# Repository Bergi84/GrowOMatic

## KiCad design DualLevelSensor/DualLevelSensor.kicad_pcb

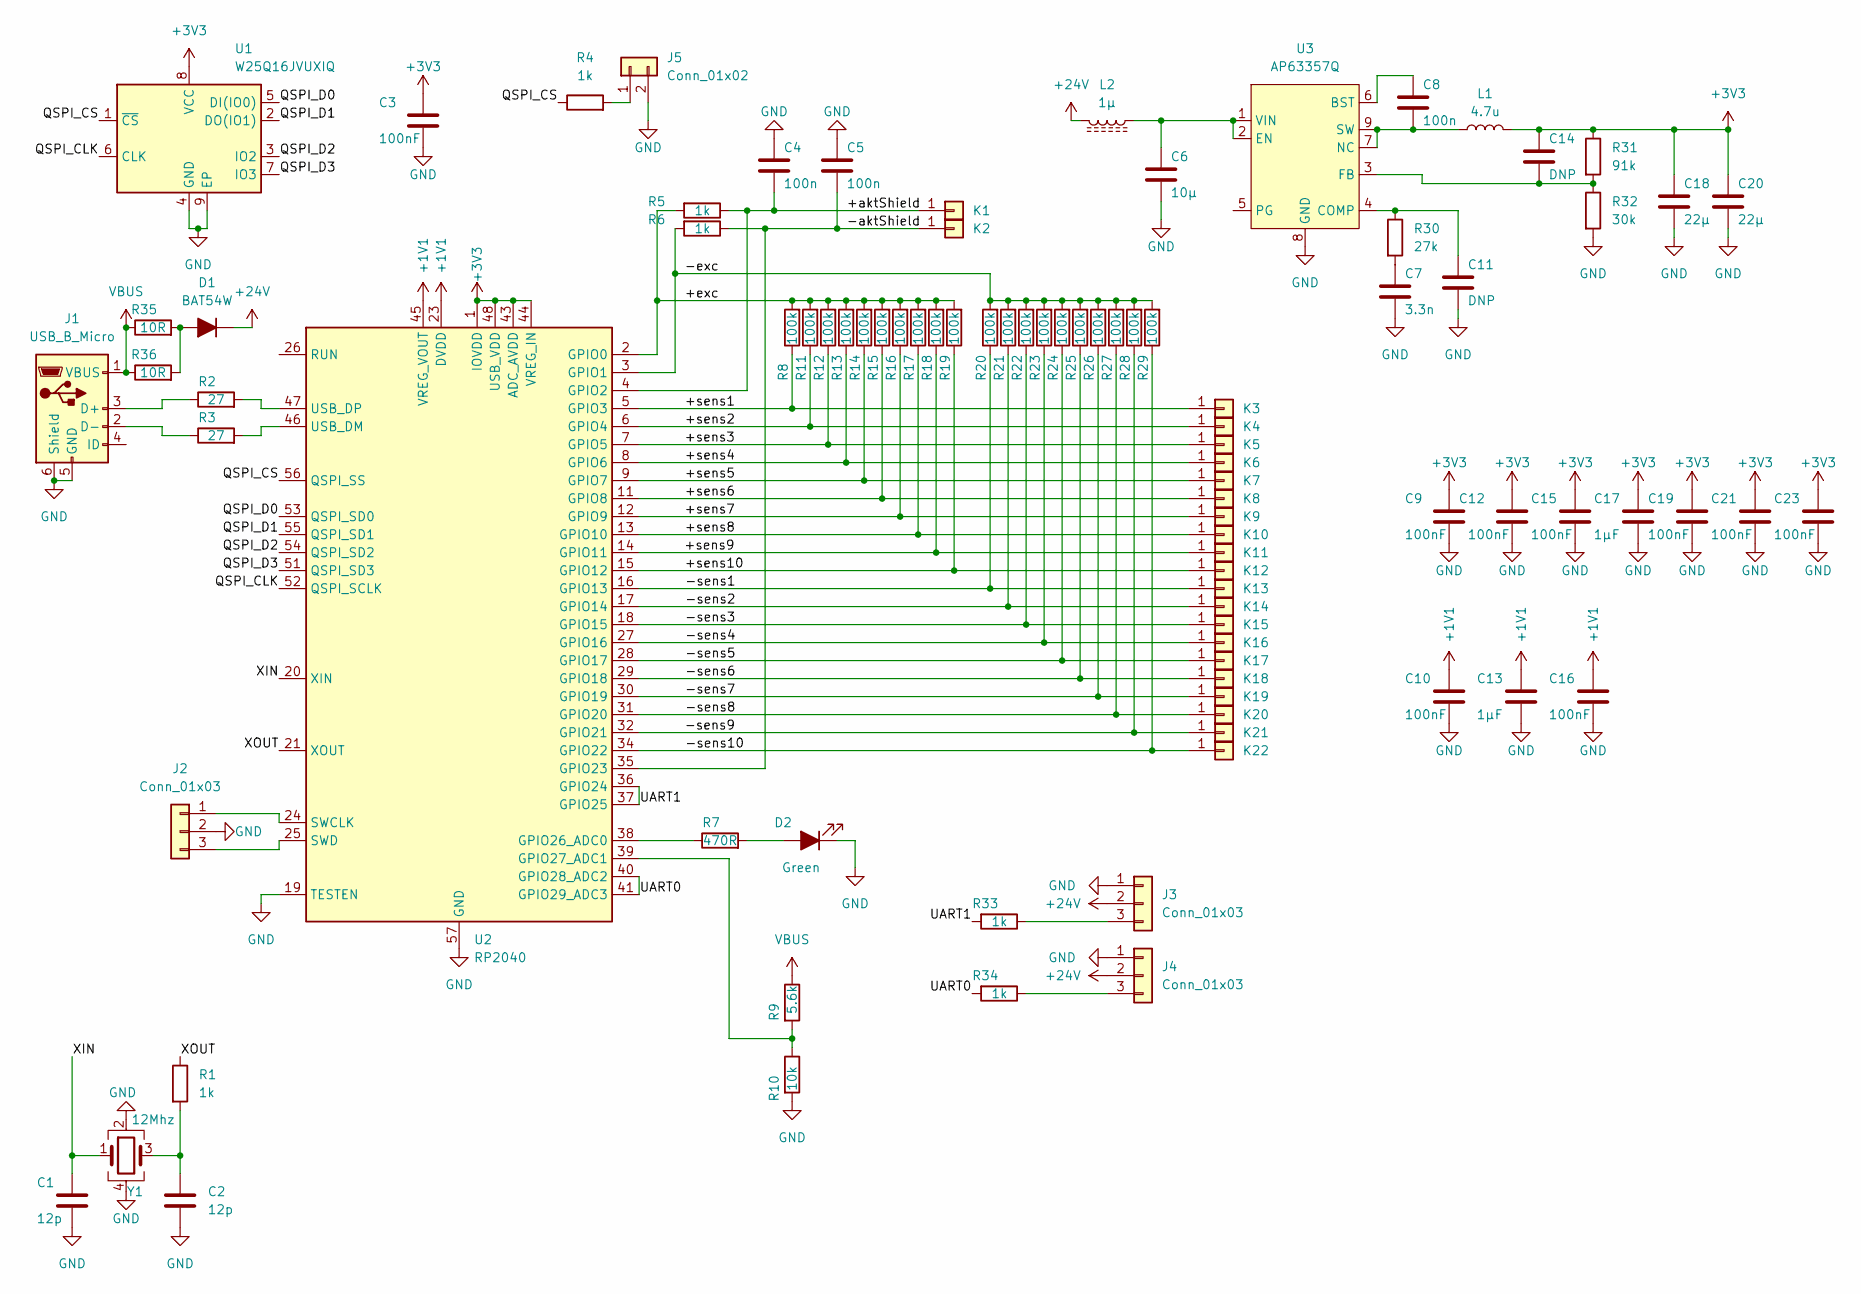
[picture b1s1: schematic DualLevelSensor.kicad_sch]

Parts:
C1, C2: 12p; C_0603_1608Metric
C3, C9, C10, C12, C15, C16, C19, C21, C23: 100nF; C_0603_1608Metric
C4, C5, C8: 100n; C_0603_1608Metric
C6: 10µ; C_1210_3225Metric
C7: 3.3n; C_0603_1608Metric
C11, C14: DNP; C_0603_1608Metric
C13, C17: 1µF; C_0603_1608Metric
C18, C20: 22µ; C_1206_3216Metric
D1: BAT54W; D_SOD-323
D2: Green; LED_0603_1608Metric
J1: USB_B_Micro; USB_Micro-B_GCT_USB3076-30-A
J2: Conn_01x03; PinHeader_1x03_P2.54mm_Vertical
J3, J4: Conn_01x03; Molex_KK-254_AE-6410-03A_1x03_P2.54mm_Vertical
J5: Conn_01x02; PinSocket_1x02_P2.54mm_Vertical
K1, K2, K3, K4, K5, K6, K7, K8, K9, K10, K11, K12, K13, K14, K15, K16, K17, K18, K19, K20, K21, K22: capPad; dummyPad
L1: 4.7u; L_1008_2520Metric
L2: 1µ; L_0805_2012Metric
R1, R4, R5, R6, R33, R34: 1k; R_0603_1608Metric
R2, R3: 27; R_0603_1608Metric
R7: 470R; R_0603_1608Metric
R8, R11, R12, R13, R14, R15, R16, R17, R18, R19, R20, R21, R22, R23, R24, R25, R26, R27, R28, R29: 100k; R_0603_1608Metric
R9: 5.6k; R_0603_1608Metric
R10: 10k; R_0603_1608Metric
R30: 27k; R_0603_1608Metric
R31: 91k; R_0603_1608Metric
R32: 30k; R_0603_1608Metric
R35, R36: 10R; R_0603_1608Metric
U1: W25Q16JVUXIQ; DFN-8-1EP_3x2mm_P0.5mm_EP0.3x1.6mm
U2: RP2040; QFN-56-1EP_7x7mm_P0.4mm_EP3.2x3.2mm
U3: AP63357Q; V-DFN3020-13
Y1: 12Mhz; Crystal_SMD_2520-4Pin_2.5x2.0mm

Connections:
+1V1: C10.1, C13.1, C16.1, U2.23 (DVDD), U2.45 (VREG_VOUT), U2.50 (DVDD)
+3V3: C3.1, C9.1, C12.1, C14.2, C15.1, C17.1, C18.2, C19.1, C20.2, C21.1, C23.1, L1.2, R31.1, U1.8 (VCC), U2.1 (IOVDD), U2.10 (IOVDD), U2.22 (IOVDD), U2.33 (IOVDD), U2.42 (IOVDD), U2.43 (ADC_AVDD), U2.44 (VREG_IN), U2.48 (USB_VDD), U2.49 (IOVDD)
+24V: D1.1 (K), J3.2, J4.2, L2.2
/+aktShield: C4.1, K1.1, R5.1, U2.4 (GPIO2)
/+exc: R5.2, R8.2, R11.2, R12.2, R13.2, R14.2, R15.2, R16.2, R17.2, R18.2, R19.2, U2.2 (GPIO0)
/+sens1: K3.1, R8.1, U2.5 (GPIO3)
/+sens2: K4.1, R11.1, U2.6 (GPIO4)
/+sens3: K5.1, R12.1, U2.7 (GPIO5)
/+sens4: K6.1, R13.1, U2.8 (GPIO6)
/+sens5: K7.1, R14.1, U2.9 (GPIO7)
/+sens6: K8.1, R15.1, U2.11 (GPIO8)
/+sens7: K9.1, R16.1, U2.12 (GPIO9)
/+sens8: K10.1, R17.1, U2.13 (GPIO10)
/+sens9: K11.1, R18.1, U2.14 (GPIO11)
/+sens10: K12.1, R19.1, U2.15 (GPIO12)
/-aktShield: C5.1, K2.1, R6.1, U2.35 (GPIO23)
/-exc: R6.2, R20.2, R21.2, R22.2, R23.2, R24.2, R25.2, R26.2, R27.2, R28.2, R29.2, U2.3 (GPIO1)
/-sens1: K13.1, R20.1, U2.16 (GPIO13)
/-sens2: K14.1, R21.1, U2.17 (GPIO14)
/-sens3: K15.1, R22.1, U2.18 (GPIO15)
/-sens4: K16.1, R23.1, U2.27 (GPIO16)
/-sens5: K17.1, R24.1, U2.28 (GPIO17)
/-sens6: K18.1, R25.1, U2.29 (GPIO18)
/-sens7: K19.1, R26.1, U2.30 (GPIO19)
/-sens8: K20.1, R27.1, U2.31 (GPIO20)
/-sens9: K21.1, R28.1, U2.32 (GPIO21)
/-sens10: K22.1, R29.1, U2.34 (GPIO22)
/QSPI_CLK: U1.6 (CLK), U2.52 (QSPI_SCLK)
/QSPI_CS: R4.1, U1.1 (~CS), U2.56 (QSPI_SS)
/QSPI_D0: U1.5 (DI(IO0)), U2.53 (QSPI_SD0)
/QSPI_D1: U1.2 (DO(IO1)), U2.55 (QSPI_SD1)
/QSPI_D2: U1.3 (IO2), U2.54 (QSPI_SD2)
/QSPI_D3: U1.7 (IO3), U2.51 (QSPI_SD3)
/UART0: R34.2, U2.40 (GPIO28_ADC2), U2.41 (GPIO29_ADC3)
/UART1: R33.2, U2.36 (GPIO24), U2.37 (GPIO25)
/XIN: C1.1, U2.20 (XIN), Y1.1
/XOUT: R1.1, U2.21 (XOUT)
GND: C1.2, C2.2, C3.2, C4.2, C5.2, C6.1, C7.1, C9.2, C10.2, C11.1, C12.2, C13.2, C15.2, C16.2, C17.2, C18.1, C19.2, C20.1, C21.2, C23.2, D2.1 (K), J1.5 (GND), J1.6 (Shield), J2.2, J3.1, J4.1, J5.2, R10.2, R32.2, U1.4 (GND), U1.9 (EP), U2.19 (TESTEN), U2.57 (GND), U3.8 (GND), Y1.2, Y1.4
unnamed: C2.1, R1.2, Y1.3
unnamed: C6.2, L2.1, U3.1 (VIN), U3.2 (EN)
unnamed: C7.2, R30.2
unnamed: C8.1, L1.1, U3.7 (NC), U3.9 (SW)
unnamed: C8.2, U3.6 (BST)
unnamed: C11.2, R30.1, U3.4 (COMP)
unnamed: C14.1, R31.2, R32.1, U3.3 (FB)
unnamed: D1.2 (A), R35.2, R36.2
unnamed: D2.2 (A), R7.2
unnamed: J1.2 (D-), R3.1
unnamed: J1.3 (D+), R2.1
unnamed: J2.1, U2.24 (SWCLK)
unnamed: J2.3, U2.25 (SWD)
unnamed: J3.3, R33.1
unnamed: J4.3, R34.1
unnamed: J5.1, R4.2
unnamed: R2.2, U2.47 (USB_DP)
unnamed: R3.2, U2.46 (USB_DM)
unnamed: R7.1, U2.38 (GPIO26_ADC0)
unnamed: R9.2, R10.1, U2.39 (GPIO27_ADC1)
VBUS: J1.1 (VBUS), R9.1, R35.1, R36.1

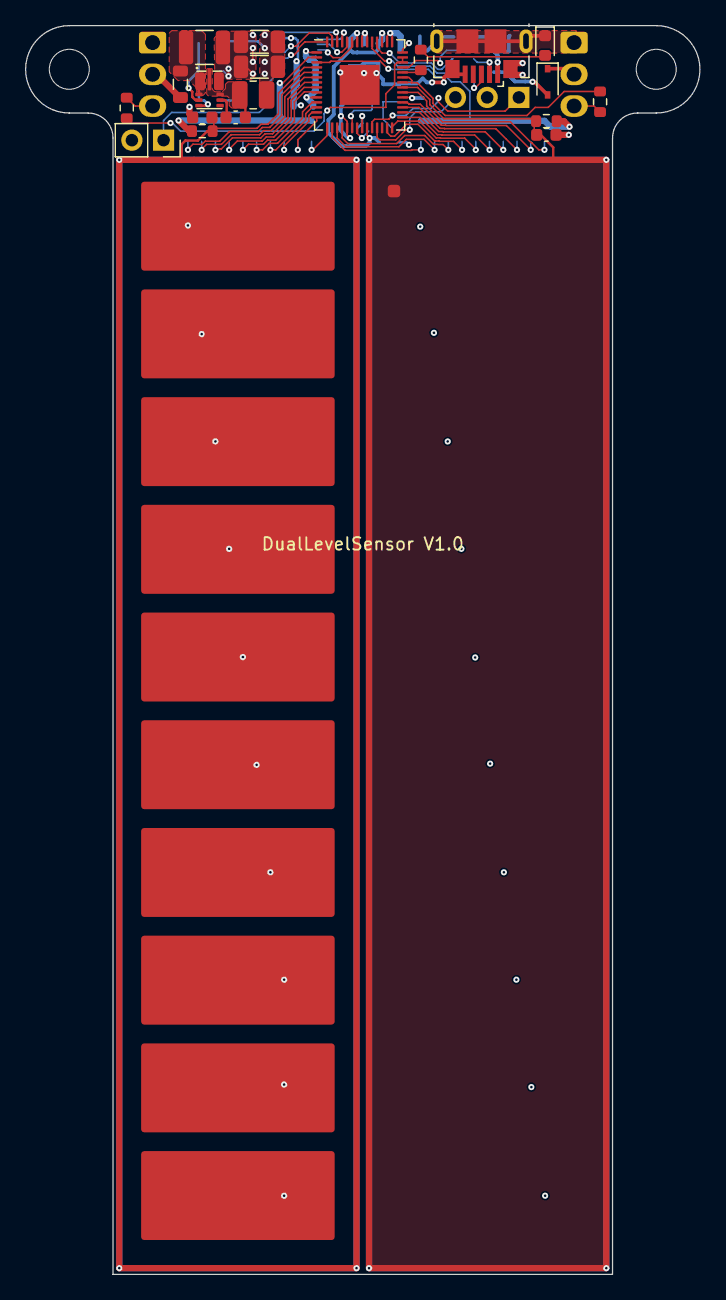
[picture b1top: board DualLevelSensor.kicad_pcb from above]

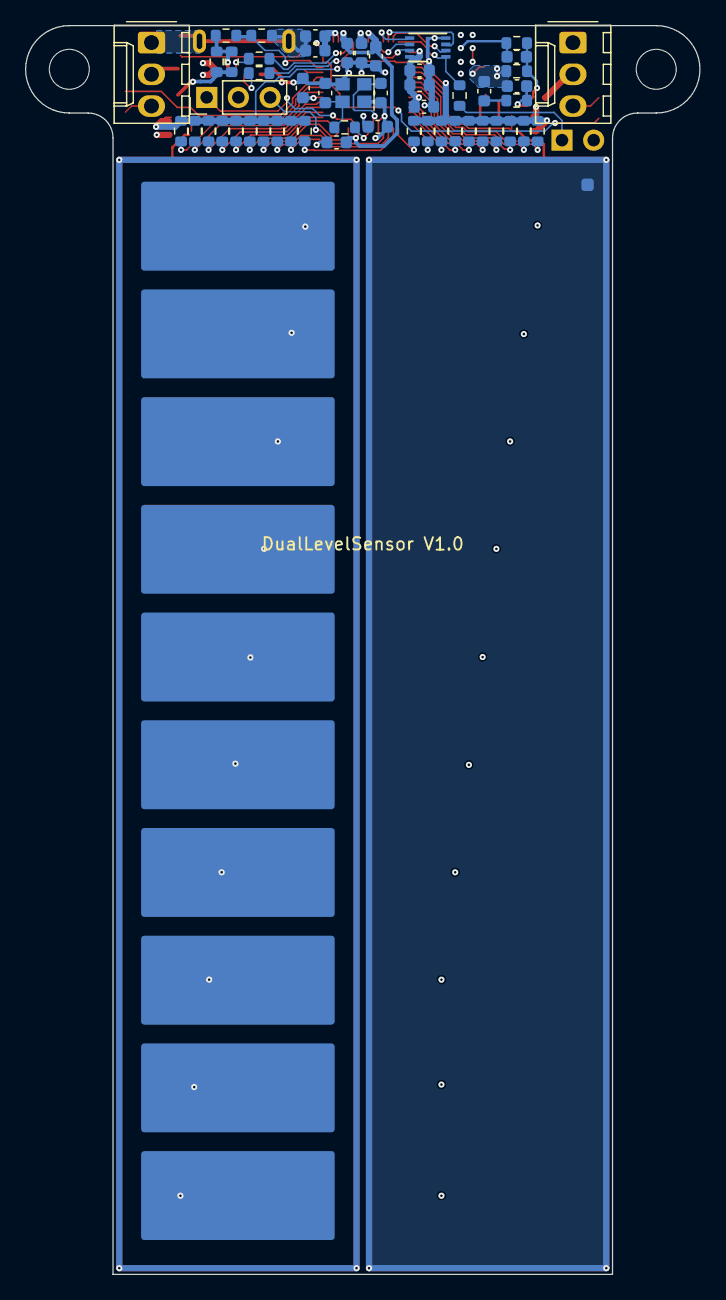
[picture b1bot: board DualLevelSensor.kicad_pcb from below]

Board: 4 copper layers, 54.0 x 100.0 mm, 95 parts (63 on the bottom side), 59 nets.

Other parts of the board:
H1, H2: MountingHole; MountingHole_3.2mm_M3_DIN965

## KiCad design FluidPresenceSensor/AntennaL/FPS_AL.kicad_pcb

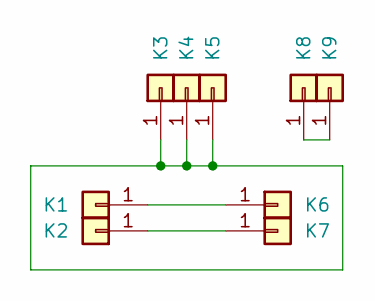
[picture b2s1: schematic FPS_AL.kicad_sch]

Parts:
K1, K2, K3, K4, K5, K6, K7, K8, K9: capPad; dummyPad

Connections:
unnamed: K1.1, K6.1
unnamed: K2.1, K7.1
unnamed: K3.1, K4.1, K5.1
unnamed: K8.1, K9.1

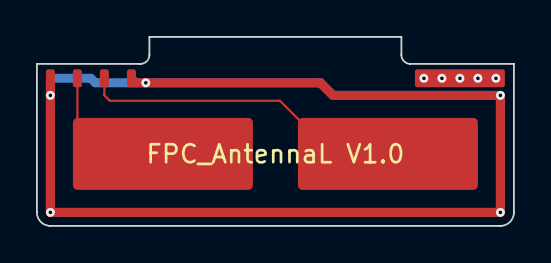
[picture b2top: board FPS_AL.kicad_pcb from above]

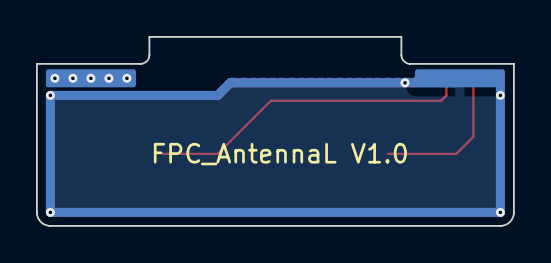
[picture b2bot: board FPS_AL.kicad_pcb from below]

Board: 2 copper layers, 26.5 x 10.5 mm, 9 parts (2 on the bottom side), 4 nets.
